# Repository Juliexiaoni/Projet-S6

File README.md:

# Projet-S6
## Objectif:

Horloge tournante à persistence rétinienne

Simuler une horloge analogique dynamique
## Planning prévisionnel

### Semaine 1 : Etude et conception

Définir les objectif (taille, résolution, affichage prévu):

- Affichage avec les 3 aiguilles

Choix des composantes (STM32, moteur, alimentation)  
Réaliser schéma électronique et mécanique   
Déterminer la fréquence de rotation optimale

### Semaine 2 : Première prototypage 

Une barrette de douze leds et le code sur le sTM32  
Branchement et alimentation puis …  
Pour faire une test avec l’ancien plaquette/moteur du projet

### Semaine 3 : Achats et fabrication du support

Acheter les composants et matériaux (Moteurs, Leds, Microprocesseur…)  
Concevoir le support du bras rotatif (PCB)  
Monter le moteur et le bras sur une base stable  
Ajouter un contrepoids pour limiter les vibrations

### Semaine 4-5 : Assemblage électronique 

### Semaine 6-7 : Programmation et Tests

### Semaine 8 : Optimisation et finalisation

## Cahier des charges

### Différentes étapes:
1. Dimensionner l’horloge 
2. développement du code en C
3. Realisation du PCB
4. Choix moteur (MCC) + axe de rotation
5. Choix des leds (blanches et rouges) → pas de driver LED
6. Choix du microcontroleur/microprocesseur 

### Matériel
1. Stm32F303K8T6
2. Moteurs https://fr.transmotec.com/product/HD3SFN-6040-CC/
3. Régulateur de tension 
4. Batterie 9V

### Tableau 

| Fonction | Critère | Niveau | Commentaires  | Qui s’en charge principalement | Avancement |
| :---- | :---- | :---- | :---- | :---- | :----|
| Mouvement le la barre de LED | Fréquence de rotation ωLED | \< 20 ms soit  \>50 Hz |  |  |  |
|  | Contact de la barre des LED’s au support | Fixe. Aucun angle de roulis ou tangage  |  |  | fait |
|  | Axe de rotation | l’axe x; mouvement plan |  |  | fait |
|  | Fixation de la barre au support  | Liaison cylindre fixé |  |  |  |
|  | Alimentation de la barre | 3.3V → pile 9V | L'entrée peut supporter jusqu’à 12 V |  |  |
|  | Codage des LED’s | Langage C valable pour STM32 |  | Julie |  |
| Moteur | Fixation du moteur au support  |  |  |  |  |
|  | Transmission ωmoteur à ωLED  |  | Idéalement aucune pertes |  | fait |
|  | Vitesse de rotation | Constante, \>3000 rpm |  |  |  |  |
| Donner l’heure  | Synchronisation des mouvements des aiguilles en fonction de l’heure  | À la seconde près  OU si on aime les défis à la ms près | Existe des modules dont le RTC | Laure |  |
|  | Affiche des aiguilles | 3 aiguilles  |  |  |  |  |
| Confort visuel | Fréquence de rotation assez élevée pour ne plus avoir de scintillement  | \>50Hz |  |  |  |
|  | Intensité des LEDs  | Fixe, indice UGR\<18 | C’est du superflu |  |  |
| Dimensions  |  | À ajuster en fonction des autres élements | Optimiser l’espace un maximum |  |  |

## Deroulé des séances

### Récapitulatif de la séance 1
1. Dimension de notre horloge (20 cm de diamètre; 3 colonnes de 12 leds en // codée individuellement et de couleur différentes)
2. choix de l'affichage de notre horloge (3 aiguilles (s:10, m:9, h:5) + indice pour se repérer sur le cadran codé sur 1 ou 2 leds sur l'aiguille de heure) #idéalement et si on a le temps 
3. micro controleur STM32Nucleo : Stm32F303K8T6
4. Determination de la fréquence (65 Hz)
5. Recherche d'un moteur MCC adéquat
6. Debut des test , notamment allumer des leds

### Objectif de la séance 2
1. realiser un premier test de frequence
2. essayer de coder une barre de LED entierement allumées et la faire tourner jusqu'à qu'il n'y a plus de scitimment

### Récapitulatif de la séance 2
1. Conception du premier prototype de PCB
2. Retour sur l'idée des trois colonnes de leds. Juste 1 de 11 LEDs => commande séparée de chacune des LEDs
3. Début de l'attribution des pattes du microcontrolleur + début du code
4. Premier essai de faire fonctionner le moteur --> Pas concluant: desaxé et inertie trop importante. 
    
#### Pour recevoir l'heure en temps réel il faut un module RTC 

### Objectifs de la séance 3
1. Trouver le bon module RTC compatible avec le micocontroleur choisi <-- on a plutôt chercher à comprendre le module RTC
2. Réaliser un premier PCB sur Kicad
3. Finaliser le code d'au moins une LED
4. Realiser un premier test en faisant touner une barre de LEDs/1 LED allumée jusqu'à plus aucun scintillemment avec le moteur

### Récapitulatif de la séance 3
1. Test avec les petits moteurs
2. Changement de STM32F303K8 --> STM32G431KBT6
3. Début du schématic de Kicad avec la STM 32 adaptée

### Objectifs de la séance 4
1. Avancer sur le prototypes des LED
2. Avancer sur le code
3. Continuer le PCB

### Récapitulatif de la séance 4
1. Prototype de la barre des LED fini
2. Premier essaie du système {moteur + barre de LED} => tourne très bien à ~ 6V mais beaucoups de vibrations
4. Test du code : problème d'IDE
5. Poursuite du schématic de Kicad 

### Objectifs de la séance 5
1. Finaliser le code pour qu'il soit fonctionnel
2. Avoir le upport pour le moteur
3. taille des trous de fixation du moteur
4. Finalisation du PCB
5. Réaliser un premier test avec les LED allumés (prototype complet)

### Recapitulatid seance 5

### Objectif séance 6

### Recapitulatif séance 6

### Objectifs séance 7

### Récapitulatif séance 8
 1. PCB entièrement fini sur Kicad
 2. test de la vitesse de rotation du moteur choisi → plus faible qu'escompté mais suffisant pour voir une image (test du laser rouge)
 3. changeant de choix d'alimentation du microcontrolleur  (2 cellules de 3,5V )
 4. Avancées du code:

### Objectif de la dernière séance (9)
 1. soudage du PCB
 2. montage global
 3. Test
 + Si le temps cache pour la pile

### Séance 9
**Problème: pas de PCB car commande trop tard**
donc programme prévue: faire le prototypage complet
## Ressources 
https://m.youtube.com/watch?v=QOkp9amAs68
https://wiki.st.com/stm32mcu/wiki/Getting_started_with_RTC

### Contacts

kessal@ensea.fr

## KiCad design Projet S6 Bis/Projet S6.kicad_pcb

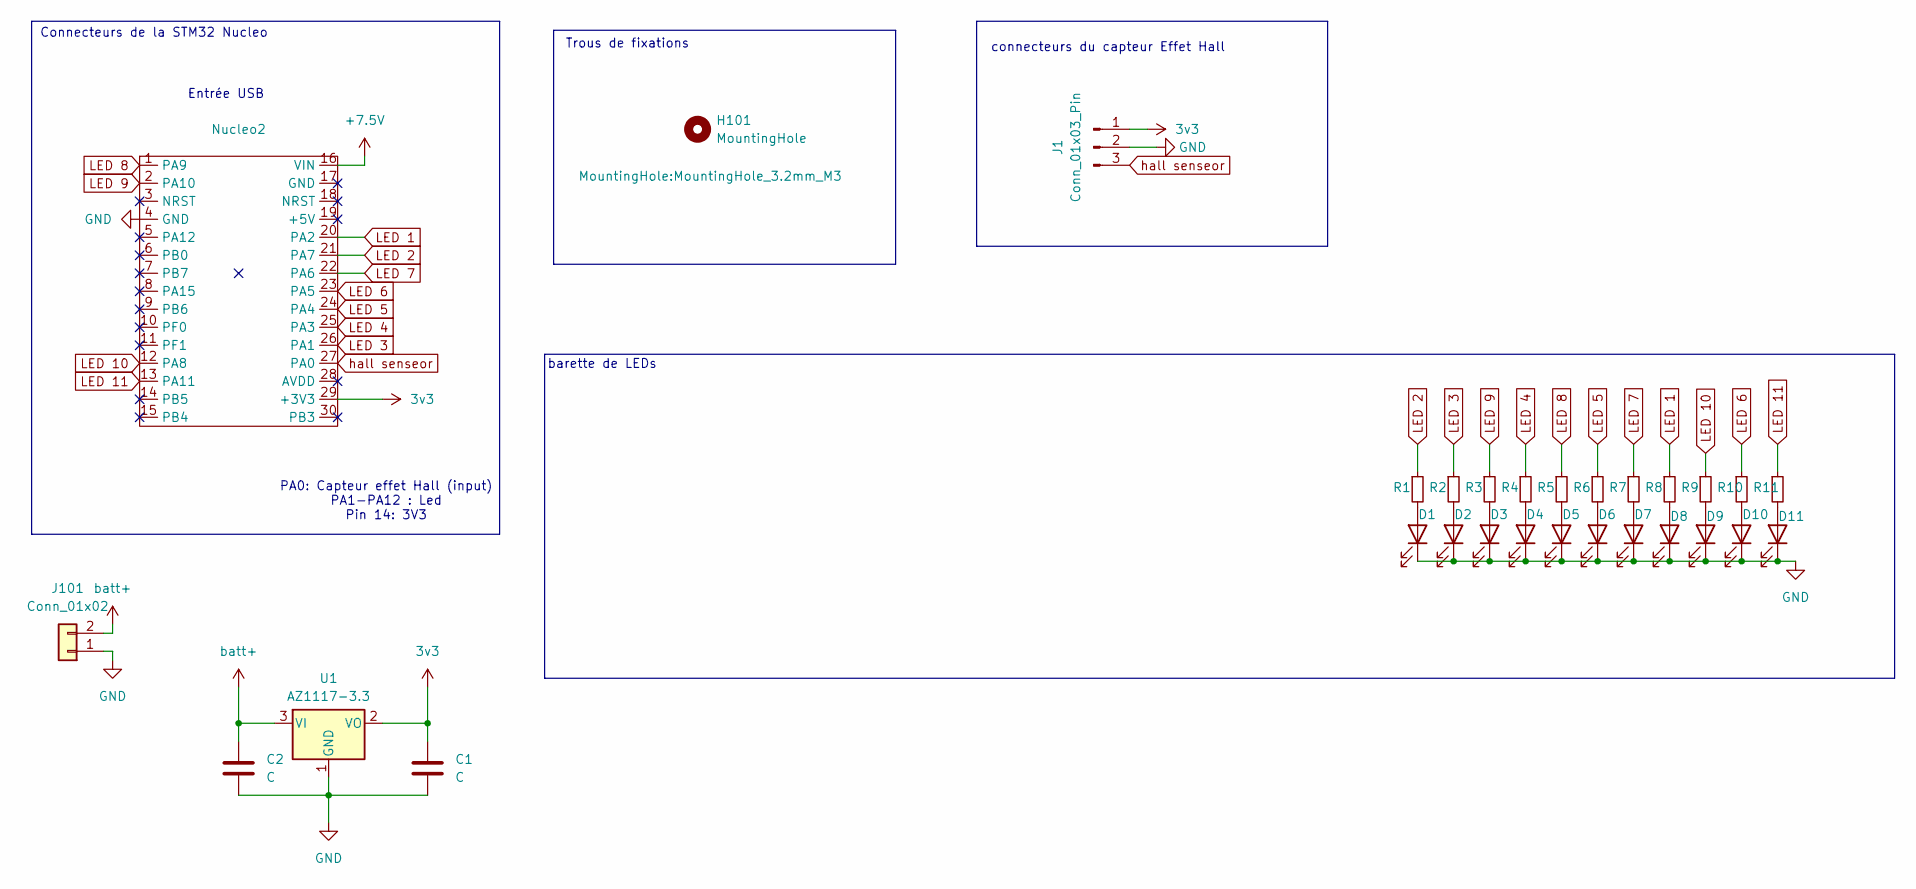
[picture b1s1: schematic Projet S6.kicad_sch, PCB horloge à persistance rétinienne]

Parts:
C1, C2: C; C_0603_1608Metric_Pad1.08x0.95mm_HandSolder
D1, D2, D3, D4, D5, D6, D7, D8, D9, D10, D11: LED; C_0402_1005Metric_Pad0.74x0.62mm_HandSolder
H101: MountingHole; MountingHole_3.2mm_M3
J1: Conn_01x03_Pin; PinHeader_1x03_P2.54mm_Vertical
J101: Conn_01x02; JST_XH_B2B-XH-AM_1x02_P2.50mm_Vertical
Nucleo2: Arduino_Nano
R1, R2, R3, R4, R5, R6, R7, R8, R9, R10, R11: 220; R_0805_2012Metric_Pad1.20x1.40mm_HandSolder
U1: AZ1117-3.3; SOT-223-3_TabPin2

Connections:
3v3: C1.1, J1.1, Nucleo2.29 (+3V3), U1.2 (VO)
+7.5V: Nucleo2.16 (VIN)
GND: C1.2, C2.2, D1.1 (K), D2.1 (K), D3.1 (K), D4.1 (K), D5.1 (K), D6.1 (K), D7.1 (K), D8.1 (K), D9.1 (K), D10.1 (K), D11.1 (K), J1.2, J101.1, Nucleo2.4 (GND), U1.1 (GND)
LED 1: Nucleo2.20 (PA2), R8.1
LED 2: Nucleo2.21 (PA7), R1.1
LED 3: Nucleo2.26 (PA1), R2.1
LED 4: Nucleo2.25 (PA3), R4.1
LED 5: Nucleo2.24 (PA4), R6.1
LED 6: Nucleo2.23 (PA5), R10.1
LED 7: Nucleo2.22 (PA6), R7.1
LED 8: Nucleo2.1 (PA9), R5.1
LED 9: Nucleo2.2 (PA10), R3.1
LED 10: Nucleo2.12 (PA8), R9.1
LED 11: Nucleo2.13 (PA11), R11.1
unnamed: D1.2 (A), R1.2
unnamed: D2.2 (A), R2.2
unnamed: D3.2 (A), R3.2
unnamed: D4.2 (A), R4.2
unnamed: D5.2 (A), R5.2
unnamed: D6.2 (A), R6.2
unnamed: D7.2 (A), R7.2
unnamed: D8.2 (A), R8.2
unnamed: D9.2 (A), R9.2
unnamed: D10.2 (A), R10.2
unnamed: D11.2 (A), R11.2
batt+: C2.1, J101.2, U1.3 (VI)
hall senseor: J1.3, Nucleo2.27 (PA0)

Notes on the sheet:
barette de LEDs
connecteurs du capteur Effet Hall
Entrée USB
PA0: Capteur effet Hall (input) PA1-PA12 : Led Pin 14: 3V3
Trous de fixations
Connecteurs de la STM32 Nucleo

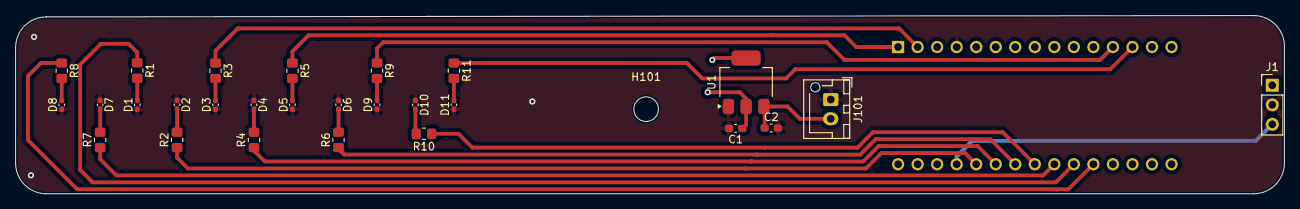
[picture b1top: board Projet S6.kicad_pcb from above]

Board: 2 copper layers, 165.0 x 23.2 mm, 29 parts (1 on the bottom side), 26 nets.

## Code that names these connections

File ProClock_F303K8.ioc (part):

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Mcu.Name=STM32F303K(6-8)Tx
Mcu.Package=LQFP32
Mcu.UserName=STM32F303K8Tx
PA0.Signal=GPIO_Input
PA1.GPIOParameters=GPIO_Speed
PA1.GPIO_Speed=GPIO_SPEED_FREQ_HIGH
PA1.Signal=GPIO_Output
PA10.GPIOParameters=GPIO_Speed
PA10.GPIO_Speed=GPIO_SPEED_FREQ_HIGH
PA10.Signal=GPIO_Output
PA11.Signal=GPIO_Output
PA13.GPIOParameters=GPIO_Label
PA13.GPIO_Label=SWDIO
PA13.Mode=Serial_Wire
PA13.Signal=SYS_JTMS-SWDIO
PA14.GPIOParameters=GPIO_Label
PA14.GPIO_Label=SWCLK
PA14.Mode=Serial_Wire
PA14.Signal=SYS_JTCK-SWCLK
PA15.Signal=S_TIM2_CH1_ETR
PA2.GPIOParameters=GPIO_Speed
PA2.GPIO_Speed=GPIO_SPEED_FREQ_HIGH
PA2.Signal=GPIO_Output
PA3.GPIOParameters=GPIO_Speed
PA3.GPIO_Speed=GPIO_SPEED_FREQ_HIGH
PA3.Signal=GPIO_Output
PA4.GPIOParameters=GPIO_Speed
PA4.GPIO_Speed=GPIO_SPEED_FREQ_HIGH
PA4.Signal=GPIO_Output
PA5.GPIOParameters=GPIO_Speed
PA5.GPIO_Speed=GPIO_SPEED_FREQ_HIGH
PA5.Signal=GPIO_Output
PA6.GPIOParameters=GPIO_Speed
PA6.GPIO_Speed=GPIO_SPEED_FREQ_HIGH
PA6.Signal=GPIO_Output
PA7.GPIOParameters=GPIO_Speed
PA7.GPIO_Speed=GPIO_SPEED_FREQ_HIGH
PA7.Signal=GPIO_Output
PA8.GPIOParameters=GPIO_Speed
PA8.GPIO_Speed=GPIO_SPEED_FREQ_HIGH
PA8.Signal=GPIO_Output
PA9.GPIOParameters=GPIO_Speed
PA9.GPIO_Speed=GPIO_SPEED_FREQ_HIGH
PA9.Signal=GPIO_Output
PF0\ /\ OSC_IN.GPIOParameters=GPIO_Label
PF0\ /\ OSC_IN.GPIO_Label=MCO
PF0\ /\ OSC_IN.Mode=HSE-External-Oscillator
PF0\ /\ OSC_IN.Signal=RCC_OSC_IN
PF1\ /\ OSC_OUT.Mode=HSE-External-Oscillator
PF1\ /\ OSC_OUT.Signal=RCC_OSC_OUT
RCC.HSEPLLFreq_Value=8000000
RCC.HSE_VALUE=8000000
RCC.SYSCLKFreq_VALUE=72000000
RCC.SYSCLKSourceVirtual=RCC_SYSCLKSOURCE_PLLCLK
board=NUCLEO-F303K8
boardIOC=true

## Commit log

2025-02-12 Mise à jour de README
2025-03-24 Code G431K8
2025-03-24 au revoir DS_Store
2025-04-29 ajout du fichier PCB
2025-04-29 PBC avec les LED 1206 et sans aucunes erreurs au DRC
2025-05-20 Correction du Timer et clignotement des LEDs
